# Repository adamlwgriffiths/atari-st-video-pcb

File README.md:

# ATARI ST Audio/Video Adapter

**NOTE: this is a work in progress and currently untested**

PCB which exposes the Audio/VGA/Composite signals more easily.

This project is an attempt to simplify the creation of audio/video adapter
cables, whilst also supporting all of the available outputs of the ATARI ST.

## What does this solve? Why should I print a PCB?

My previous attempt used a VGA Male/Male cable.
This proved to be incredibly difficult.
* VGA cables are double shielded, very stiff, and hard to work with.
* The currently available DIN 13 connectors from China have solid pins rather than cups and require Dremel'ing to make soldering possible.
* The DIN 13 connectors don't give you much room to work with before wiring starts hanging out.
* The switching gets messier the more outputs you support.
* Once mounted into a box, you cannot remove any component without de-soldering
everything.

You can purchase custom made cables online, but the workmanship is just not up to my standard.
These cables are time consuming to produce, so unless you're willing to pay for the number of hours it takes to produce a high quality cable, you're going to have to deal with the reduced quality.
With some cables you cannot view the workmanship inside without destroying the cable itself, so they are unknown quality.

What this project gives you:
* Cheaper
  * Printing this PCB comes to around $11 USD for 5 boards - including shipping.
  * Print en-masse, reduce costs, increase quality.
* Higher Quality
  * PCB already works. No need to figure out wiring diagrams, just solder the connectors and plug things in.
  * Off-the-shelf cables and connectors with simple wiring.
  * Factory assembled cables have better strain-relief / quality.
  * Easier to source.
* Simpler
  * Using standard cables (DIN 13, VGA, RCA/Composite, 2.5mm Audio).
  * Using case mounts rather than PCB mounts lets you use various sized cases
  * Connector pins and cables are mapped 1:1. Spotting mistakes is trivial.
  * Re-wiring connectors is easy if something is incorrect.
  * Remove the fiddly wiring by handling it in a PCB.
  * With a basic soldering iron you can get this done easily.
* Modular
  * Optional outputs. Don't want composite video? Don't use it.
  * Connectors on the PCB make construction and dis/assembly easy.
* Functional
  * Supports toggling between High resolution Mono and Medium resolution Colour.
  * VGA, Composite video, and Audio outputs are all accessible.
* Accessible
  * Not reliant on just a few custom builders.
  * DIN 13 Cables still used in Hi-Fi equipment.

## PCB Images

Schematic

Front

Rear

## TODO
* Provide component names for the cables for the above connectors
* Create a test version
  * Verify no resistors needed?
* Export to PCB printer supported formats
* Calculate a minimum box size required for PCB + component clearance
* Design a 3D printable case
* Provide list of steps required to build
* Provide wiring diagram for components
* Provide photos of completed box

## Parts Needed

* This PCB printed
* A suitable case
* 4x 6.35mm adhesive PCB standoffs (4mm diameter pin)

Connectors:
* 1x DIN 13 Female case mount
* 1x VGA DB15 Female case mount
* 1x 2.5mm Audio Jack Female case mount
* 1x 4P2T Switch (2x4 inputs, 1x4 outputs)
* 3x JST EH B4B-EH-A 2.5mm connector (4-pin connector)
* 1x JST EH B13B-EH-A 2.5mm connector (13-pin connector)
* 1x JST EH B15B-EH-A 2.5mm connector (15-pin connector) (For VGA Output)
* 1x JST EH B2B-EH-A 2.5mm connector (2-pin connector) (For Composite Video Output)
* 1x JST EH B3B-EH-A 2.5mm connector (3-pin connector) (For Audio Output)

Internal Cabling:
* TODO: Provide component names for the cables for the above connectors

Cables and External Peripherals:
* 1x DIN 13 Male/Male cable
* 1x VGA cable
* 1x 2.5mm Audio cable (I recommend the ALogic VGA cables with integrated 2.5mm audio)
* 3x RCA Male/Male cable (1x for video, 2x for audio) (For Composite Video / Audio Output)
* 1x 2.5mm -> RCA converter
* GBS-8200 VGA converter or equivalent (required as the video output from Atari ST uses a non-standard frequency)

### Sourcing Parts

DIN 13 components are hard to come by.
I found the following on eBay:
* [DIN 13 Female case mount](https://www.ebay.com/itm/390671564763).
* [DIN 13 Male/Male cable](https://www.ebay.com/itm/133246734205).

GBS-8200 are readily available on eBay or AliExpress.

### GBS-8200

Be aware they often need minor modification with Copper tape to remove noise.
See [this video](https://youtu.be/q3J4QJsn0ig?t=389) for more information on this issue and how to improve it.

## Construction

1. Source all the required parts
2. Solder the PCB mount connectors to the PCB
3. Cut holes into the case for the following connectors
 * DIN 13
 * 4P2T switch
 * VGA
 * RCA/Composite
 * 2.5mm Audio
4. Mount the connectors
5. Solder the cables to the connectors
6. Mount the PCB in the case
  * Place the adhesive standoffs in the PCB mounting holes
  * Remove the adhesive cover
  * Place the PCB into the case and press down firmly
7. Connect the cables to the PCB
8. Set the switch the mono or colour (usually the switch is moved to the side opposite the desired input wires)
9. Close the case

## Tools Used

The PCB is designed using [KiCAD](https://www.kicad.org/).

## Discussion

### Can I not use the {VGA,Composite,Audio} output and just use {VGA,Composite,Audio} instead?

Yes, whatever floats your boat.

### Couldn't you make the connectors smaller by dropping the unused pins?

Yes. I feel it is easier cognitively to just wire it all up and have the PCB route them no where.

The following pins are unused, feel free to just not connect these pins if you so choose.

J1 (DIN 13): 3, 5, 8
J2 (VGA): 4, 9, 11, 12, 15

### The size of the connectors means the case mounts can't be removed without desoldering

Yes. But this is trivial compared to working with VGA cables or having to re-work the switching logic.

### Couldn't you use PCB mounted connectors to simplify some of this?

Yes, but that makes case selection difficult.

Feel free to do this yourself.

### Can I just solder the wires directly to the PCB

Yep.

### Isn't this over-engineered?

Maybe.

## References

This project is based on the schematic designed by [BackOfficeShow](http://www.backofficeshow.com/) and presented in [this video](https://www.youtube.com/watch?v=N9xhNgCW2LQ)

Wiring diagram extracted from video:

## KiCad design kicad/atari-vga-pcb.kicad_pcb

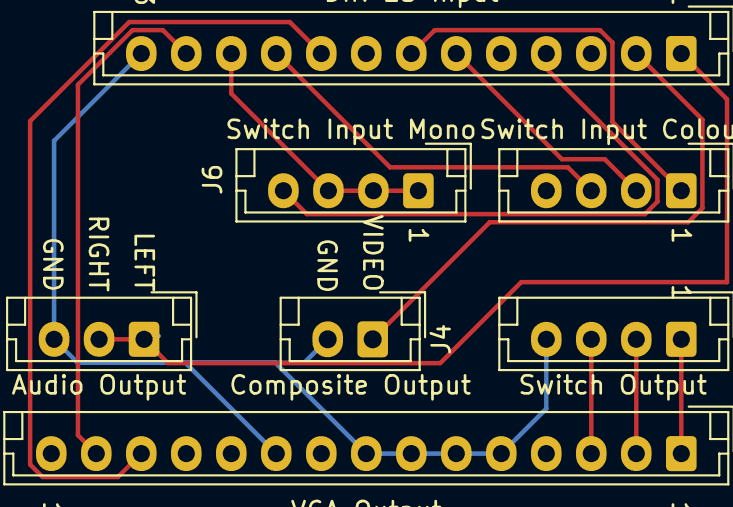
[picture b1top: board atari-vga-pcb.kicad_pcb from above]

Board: 2 copper layers, 7 parts (0 on the bottom side), 13 nets.

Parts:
J1: DIN 13 Input; JST_EH_B13B-EH-A_1x13_P2.50mm_Vertical
J2: VGA Output; JST_EH_B15B-EH-A_1x15_P2.50mm_Vertical
J3: Audio Output; JST_EH_B3B-EH-A_1x03_P2.50mm_Vertical
J4: Composite Output; JST_EH_B2B-EH-A_1x02_P2.50mm_Vertical
J5: Switch Input Colour; JST_EH_B4B-EH-A_1x04_P2.50mm_Vertical
J6: Switch Input Mono; JST_EH_B4B-EH-A_1x04_P2.50mm_Vertical
J7: Switch Output; JST_EH_B4B-EH-A_1x04_P2.50mm_Vertical

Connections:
unnamed: J1.1, J3.1, J3.2
unnamed: J1.2, J4.1
unnamed: J1.4, J6.4
unnamed: J1.6, J5.2
unnamed: J1.7, J5.1
unnamed: J1.9, J2.13
unnamed: J1.10, J5.3
unnamed: J1.11, J6.1, J6.2, J6.3
unnamed: J1.12, J2.14
unnamed: J1.13, J2.5, J2.6, J2.7, J2.8, J2.10, J3.3, J4.2, J7.4
unnamed: J2.1, J7.1
unnamed: J2.2, J7.2
unnamed: J2.3, J7.3

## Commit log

2020-12-28 Initial PCB layout and information. UNTESTED.
    Still need to:
    * Test
    * Verify no resistors needed
    * Export to PCB printer supported formats
    * Design a 3D printable case
    * Provide wiring diagram for components
